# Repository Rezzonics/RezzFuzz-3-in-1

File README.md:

# RezzFuzz-3-in-1
Rezz-Fuzz 3 in 1: RAT + βr + Octaver

Eagle CAD files: 
  - Schematics 
  - BoM 
  - PCB 
  - Gerbers

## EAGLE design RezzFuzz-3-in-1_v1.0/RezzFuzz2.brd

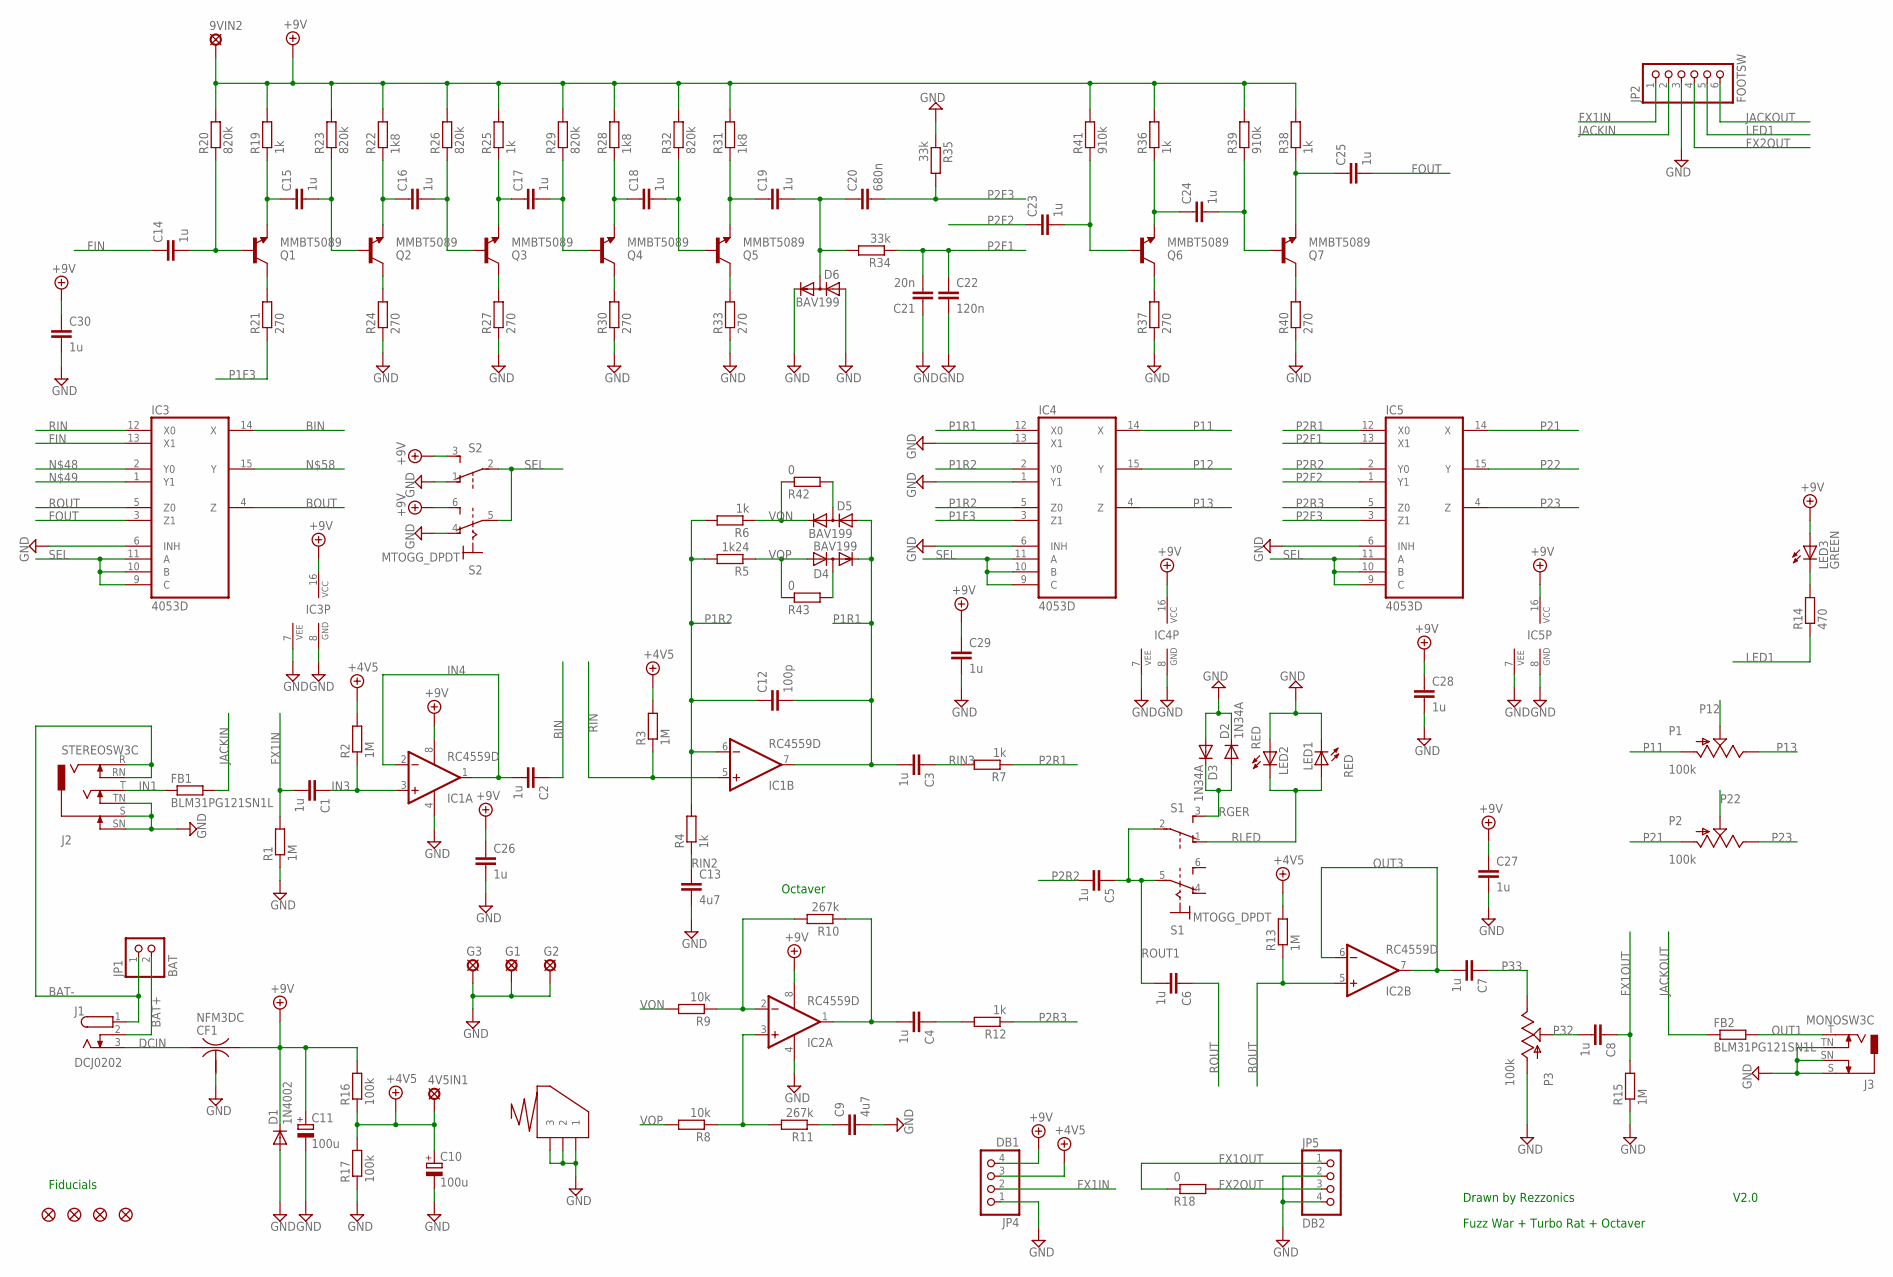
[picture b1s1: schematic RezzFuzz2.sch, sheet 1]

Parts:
4V5IN1, 9VIN2: LSP13; MPN *
BS1: CLIPAAA-; MPN *
C1, C2, C3, C4, C5, C6, C7, C8, C14, C15, C16, C17, C18, C19, C23, C24, C25, C26, C27, C28, C29, C30: 1u; C0603; MPN GRM188R61E105KA12J
C9, C13: 4u7; C0805; MPN GRM21BR61E475MA12L
C10, C11: 100u; PANASONIC_D; MPN AVE107M25X16T-F
C12: 100p; C0603; MPN VJ0603Y101MXXCW1BC
C20: 680n; C0603; MPN C0603C684K4PACTU
C21: 20n; C0603; MPN VJ0603Y223KXXCW1BC
C22: 120n; C0603; MPN GRM188R71E124KA01D
CF1: NFM3DC; MPN NFM3DPC223R1H3L
D1: 1N4002; DO41-7.6; MPN 1N4002E-E3/73
D2, D3: 1N34A; DO35-7; MPN 1n34A
D4, D5, D6: BAV199; SOT23; MPN BAV199,235
FB1, FB2: BLM31PG121SN1L; R1206; MPN BLM31PG121SN1L
G1, G2, G3: LSP13; MPN *
IC1, IC2: RC4559D; SO08; MPN RC4559DE4
IC3, IC4, IC5: 4053D; SO16; MPN CD4053BM96G3
J1: DCJ0202; MPN 163-179PH-EX
J2: STEREOSW3C; NEUTRIK-NMJ6HCD2; MPN NMJ6HCD2
J3: MONOSW3C; NEUTRIK-NMJ4HCD2; MPN NMJ4HCD2
JP1: BAT; 1X02; MPN 929834-01-02-RK
JP2: FOOTSW; 1X06; MPN 929834-01-04-RK
JP3, JP6, JP7, JP8: FIDUCIAL1X2.5; FIDUCIAL-1X2.5; MPN *
JP4: DB1; 1X04; MPN 929834-01-04-RK
JP5: DB2; 1X04; MPN 929834-01-04-RK
LED1, LED2: RED; CHIPLED_1206; MPN 598-8210-107F
LED3: GREEN; LED5MM; MPN C5SMF-GJS-CV14Q7S1
P1, P2: 100k; POT_MAMMOTH; MPN RV16AF-41-15R1-B100K
P3: 100k; POT_MAMMOTH; MPN RV16AF-41-15R1-A100K
Q1, Q2, Q3, Q4, Q5, Q6, Q7: MMBT5089; SOT23; MPN MMBT5089
R1, R2, R3, R13, R15: 1M; R0603; MPN CR0603-FX-1004ELF
R4: 1k; R0603; MPN CR0603-FX-1004ELF
R5: 1k24; R0603; MPN CR0603-FX-1241ELF
R6, R7, R12: 1k; R0603; MPN CR0603-FX-1001HLF
R8, R9: 10k; R0603; MPN CR0603-FX-1002HLF
R10, R11: 267k; R0603; MPN CR0603-FX-2673ELF
R14: 470; R0603; MPN CR0603-FX-4700ELF
R16, R17: 100k; R0603; MPN CR0603-FX-1003ELF
R18, R42, R43: 0; R0603; MPN CRCW06030000ZSTB
R19, R25: 1k; R0603; MPN CR0603-FX-1003ELF
R20, R23, R26, R29, R32: 820k; R0603; MPN CR0603-FX-4303ELF
R21, R24, R27, R30, R33, R37, R40: 270; R0603; MPN CR0603-FX-3900ELF
R22, R28, R31: 1k8; R0603; MPN CR0603-FX-1803ELF
R34, R35: 33k; R0603; MPN CR0603-FX-3302ELF
R36, R38: 1k; R0603; MPN CR0603-FX-1803ELF
R39, R41: 910k; R0603; MPN CR0603-FX-9103ELF
S1: MTOGG_DPDT; MTOGGLE_DPDT; MPN M2023SS1W03
S2: MTOGG_DPDT; MTOGGLE_DPDT; MPN M2022SS1W03

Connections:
+4.5V: 4V5IN1.MP, C10.+, JP4.3, R2.2, R3.2, R13.2, R16.1, R17.2
+9V: 9VIN2.MP, C11.+, C26.1, C27.1, C28.1, C29.1, C30.1, CF1.3, D1.C, IC1.8 (V+), IC2.8 (V+), IC3.16 (VCC), IC4.16 (VCC), IC5.16 (VCC), JP4.4, LED3.A, R16.2, R19.2, R20.2, R22.2, R23.2, R25.2, R26.2, R28.2, R29.2, R31.2, R32.2, R36.2, R38.2, R39.2, R41.2, S2.3 (S), S2.6 (S)
BAT+: J1.2, JP1.2
BAT-: J1.1, J2.R, J2.RN, JP1.1
BIN: C2.1, IC3.14 (X)
BOUT: IC2.5 (+IN), IC3.4 (Z), R13.1
DCIN: CF1.1, J1.3
FIN: C14.1, IC3.13 (X1)
FOUT: C25.2, IC3.3 (Z1)
FX1IN: C1.2, JP2.1, JP4.2, R1.2
FX1OUT: C8.1, JP5.1, R15.2, R18.1
FX2OUT: JP2.4, JP5.3, R18.2
GND: BS1.1, BS1.2, BS1.3, C9.2, C10.-, C11.-, C13.2, C21.1, C22.2, C26.2, C27.2, C28.2, C29.2, C30.2, CF1.2@1 (2), D1.A, D2.C, D3.A, D6.1 (A), D6.2 (C), G1.MP, G2.MP, G3.MP, IC1.4 (V-), IC2.4 (V-), IC3.6 (INH), IC3.7 (VEE), IC3.8 (GND), IC4.1 (Y1), IC4.6 (INH), IC4.7 (VEE), IC4.8 (GND), IC4.13 (X1), IC5.6 (INH), IC5.7 (VEE), IC5.8 (GND), J2.S, J2.SN, J2.TN, J3.S, J3.SN, J3.TN, JP2.3, JP4.1, JP5.2, JP5.4, LED1.C, LED2.A, P3.P$1 (A), R1.1, R15.1, R17.1, R24.1, R27.1, R30.1, R33.1, R35.1, R37.1, R40.1, S2.1 (O), S2.4 (O)
IN1: FB1.1, J2.T
IN3: C1.1, IC1.3 (+IN), R2.1
IN4: C2.2, IC1.1 (OUT), IC1.2 (-IN)
JACKIN: FB1.2, JP2.2
JACKOUT: FB2.1, JP2.6
LED1: JP2.5, R14.1
unnamed: C14.2, Q1.1 (B), R20.1
unnamed: Q1.3 (C), R21.2
unnamed: C16.1, Q2.2 (E), R22.1
unnamed: Q2.3 (C), R24.2
unnamed: C16.2, Q3.1 (B), R26.1
unnamed: C17.1, Q3.2 (E), R25.1
unnamed: IC2.3 (+IN), R8.1, R11.2
unnamed: IC2.2 (-IN), R9.1, R10.2
unnamed: C9.1, R11.1
unnamed: C4.2, IC2.1 (OUT), R10.1
unnamed: C4.1, R12.2
unnamed: Q3.3 (C), R27.2
unnamed: C17.2, Q4.1 (B), R29.1
unnamed: C18.1, Q4.2 (E), R28.1
unnamed: Q4.3 (C), R30.2
unnamed: C18.2, Q5.1 (B), R32.1
unnamed: C19.1, Q5.2 (E), R31.1
unnamed: D5.3 (AC), R42.2
unnamed: Q5.3 (C), R33.2
unnamed: C19.2, C20.1, D6.3 (AC), R34.2
unnamed: C24.2, Q7.1 (B), R39.1
unnamed: C23.2, Q6.1 (B), R41.1
unnamed: C24.1, Q6.2 (E), R36.1
unnamed: C25.1, Q7.2 (E), R38.1
unnamed: Q7.3 (C), R40.2
unnamed: Q6.3 (C), R37.2
unnamed: LED3.K (C), R14.2
unnamed: C15.2, Q2.1 (B), R23.1
unnamed: D4.3 (AC), R43.2
unnamed: C15.1, Q1.2 (E), R19.1
OUT1: FB2.2, J3.T
OUT3: C7.2, IC2.6 (-IN), IC2.7 (OUT)
P1F3: IC4.3 (Z1), R21.1
P1R1: C3.2, C12.2, D4.2 (C), D5.1 (A), IC1.7 (OUT), IC4.12 (X0)
P1R2: C12.1, IC1.6 (-IN), IC4.2 (Y0), IC4.5 (Z0), R4.2, R5.2, R6.2
P2F1: C21.2, C22.1, IC5.13 (X1), R34.1
P2F2: C23.1, IC5.1 (Y1)
P2F3: C20.2, IC5.3 (Z1), R35.2
P2R1: IC5.12 (X0), R7.1
P2R2: C5.2, IC5.2 (Y0)
P2R3: IC5.5 (Z0), R12.1
P11: IC4.14 (X), P1.P$1 (A)
P12: IC4.15 (Y), P1.P$2 (S)
P13: IC4.4 (Z), P1.P$3 (E)
P21: IC5.14 (X), P2.P$1 (A)
P22: IC5.15 (Y), P2.P$2 (S)
P23: IC5.4 (Z), P2.P$3 (E)
P32: C8.2, P3.P$2 (S)
P33: C7.1, P3.P$3 (E)
RGER: D2.A, D3.C, S1.3 (S)
RIN: IC1.5 (+IN), IC3.12 (X0), R3.1
RIN2: C13.1, R4.1
RIN3: C3.1, R7.2
RLED: LED1.A, LED2.C, S1.1 (O)
ROUT: C6.1, IC3.5 (Z0)
ROUT1: C5.1, C6.2, S1.2, S1.5
SEL: IC3.9 (C), IC3.10 (B), IC3.11 (A), IC4.9 (C), IC4.10 (B), IC4.11 (A), IC5.9 (C), IC5.10 (B), IC5.11 (A), S2.2, S2.5
VON: D5.2 (C), R6.1, R9.2, R42.1
VOP: D4.1 (A), R5.1, R8.2, R43.1

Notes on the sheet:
Drawn by Rezzonics
Octaver
Fiducials
V2.0
Fuzz War + Turbo Rat + Octaver

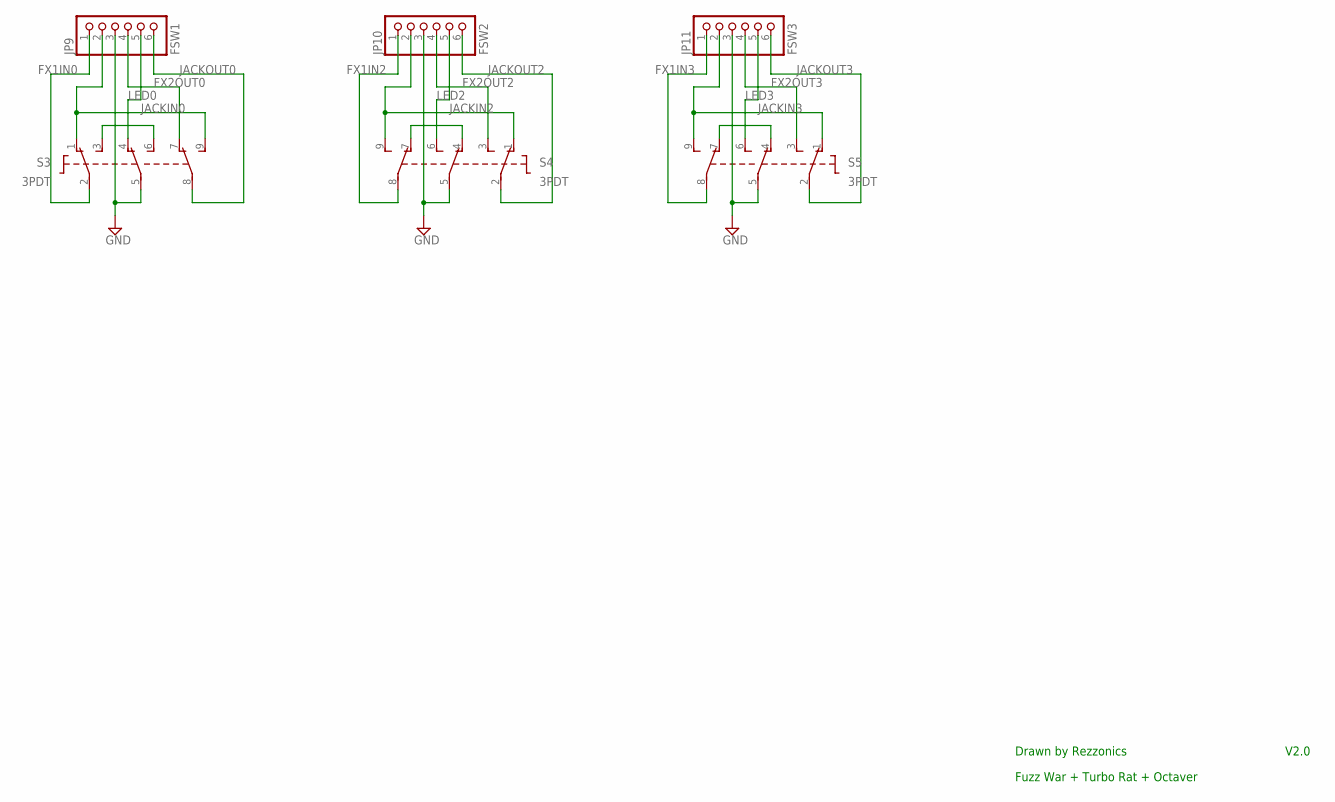
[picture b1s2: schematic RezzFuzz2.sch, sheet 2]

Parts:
JP9: FSW1; 1X06; MPN *
JP10: FSW2; 1X06; MPN *
JP11: FSW3; 1X06; MPN *
S3, S4, S5: 3PDT; MPN *

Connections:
FX1IN0: JP9.1, S3.2 (P1)
FX1IN2: JP10.1, S4.8 (P3)
FX1IN3: JP11.1, S5.8 (P3)
FX2OUT0: JP9.4, S3.7 (O3)
FX2OUT2: JP10.4, S4.3 (S1)
FX2OUT3: JP11.4, S5.3 (S1)
GND1: JP9.3, S3.5 (P2)
GND2: JP10.3, S4.5 (P2)
GND3: JP11.3, S5.5 (P2)
JACKIN0: JP9.2, S3.1 (O1), S3.9 (S3)
JACKIN2: JP10.2, S4.1 (O1), S4.9 (S3)
JACKIN3: JP11.2, S5.1 (O1), S5.9 (S3)
JACKOUT0: JP9.6, S3.8 (P3)
JACKOUT2: JP10.6, S4.2 (P1)
JACKOUT3: JP11.6, S5.2 (P1)
LED0: JP9.5, S3.4 (O2)
LED2: JP10.5, S4.6 (S2)
LED3: JP11.5, S5.6 (S2)
unnamed: S3.3 (S1), S3.6 (S2)
unnamed: S4.4 (O2), S4.7 (O3)
unnamed: S5.4 (O2), S5.7 (O3)

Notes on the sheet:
Drawn by Rezzonics
V2.0
Fuzz War + Turbo Rat + Octaver

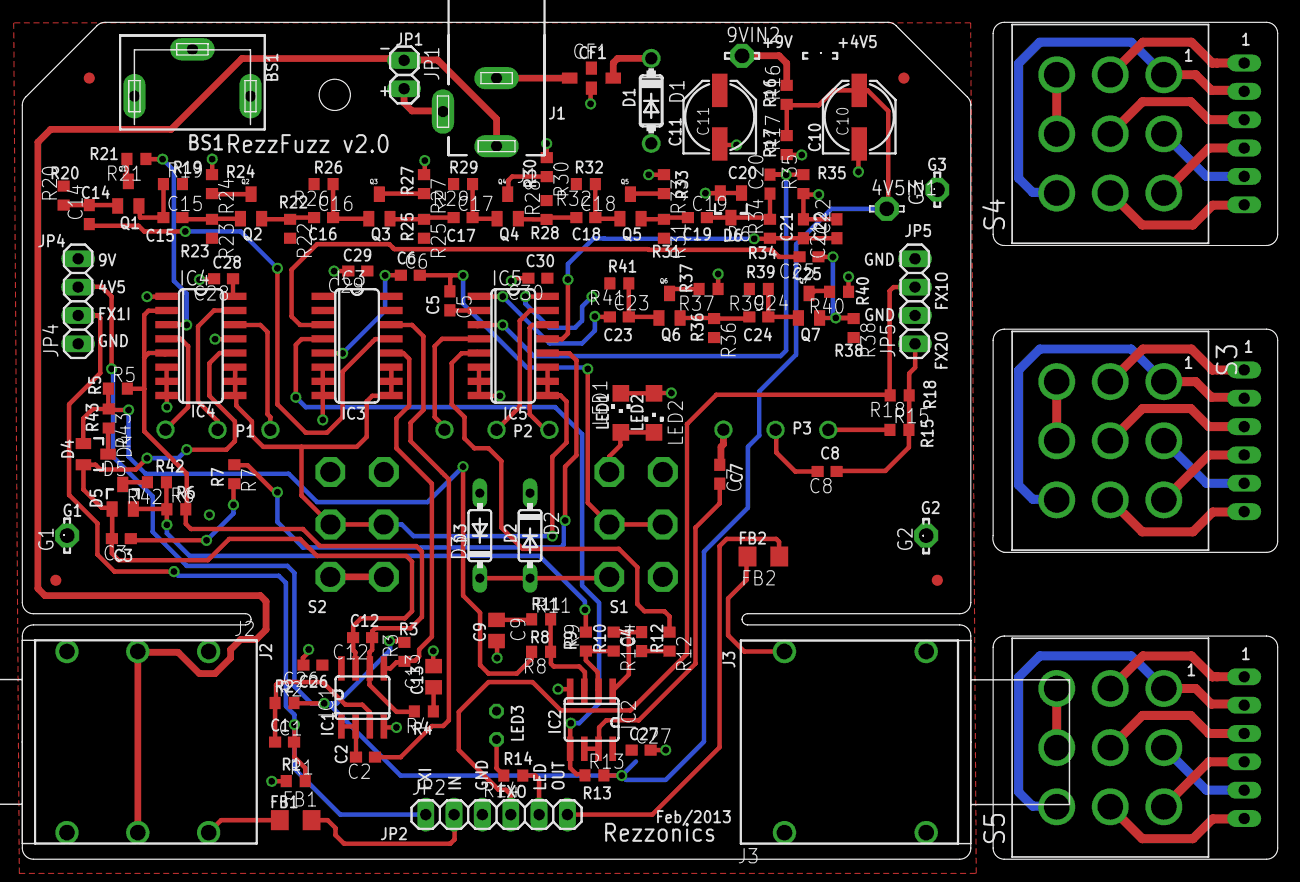
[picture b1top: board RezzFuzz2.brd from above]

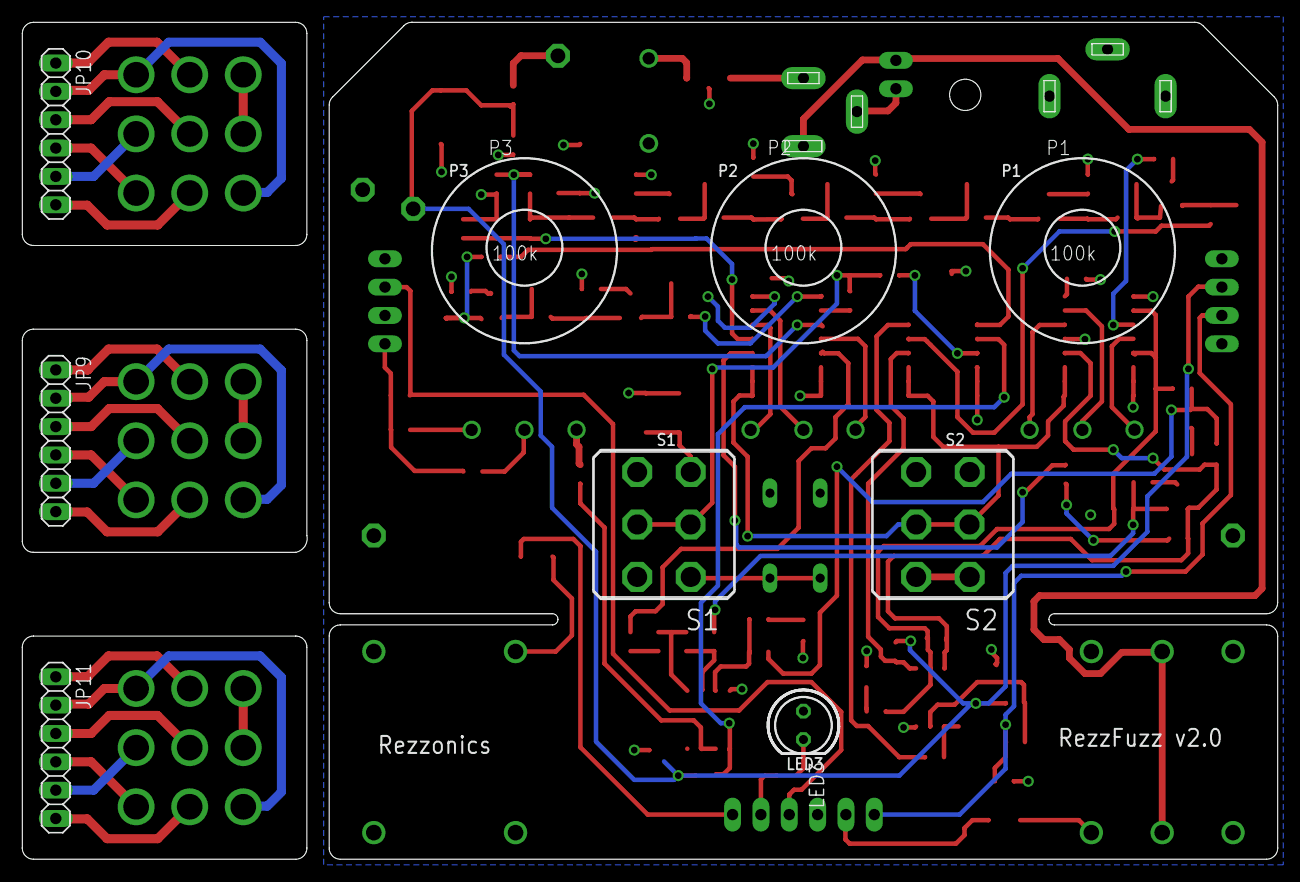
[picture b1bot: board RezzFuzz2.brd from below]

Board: 2 copper layers, 85.0 x 75.0 mm, 125 parts (9 on the bottom side), 99 nets.

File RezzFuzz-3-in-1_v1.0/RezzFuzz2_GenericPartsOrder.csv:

Part Number,Mfg Name,VID,Vendor Part Num,Description,Customer Ref,Part Value,Tol,Qty-1,Qty-5,Qty-25,Part References,Value
CRCW06030000ZSTB,Vishay,ME,71-CRCW0603000ZT-RT5,Thick Film Resistors - SMD 1/10watt ZEROohm Jumper,res013,0,*,3,15,75,"R18, R42, R43",0
CR0603-FX-1003ELF,Bourns,ME,652-CR0603-FX-103ELF,Thick Film Resistors - SMD 100K 1% 1/10 WATT,res004,100k,*,1,5,25,"R25",1.2k
CR0603-FX-1803ELF,Bourns,ME,652-CR0603FX-1803ELF,Thick Film Resistors - SMD 180K 1% 1/10W,res006,180k,*,5,25,125,"R22, R28, R31, R36, R38",1.2k
CR0603-FX-1004ELF,Bourns,ME,652-CR0603FX-1004ELF,Thick Film Resistors - SMD 1M 1% 1/10W,res003,1M,*,5,25,125,"R1, R2, R3, R13, R15",1M
*** ERROR - PART '1n34A' NOT FOUND FOR: "D2, D3"
1N4002E-E3/73,Vishay,ME,625-1N4002E-E3/73,Rectifiers Vr/100V Io/1A,diode001,*,*,1,5,25,"D1",1N4002
CR0603-FX-1001HLF,Bourns,ME,652-CR0603-FX1001HLF,Thick Film Resistors - SMD 1KOHM 1/10WATT 1%,res001,1k,*,3,15,75,"R6, R7, R12",1k
CR0603-FX-1004ELF,Bourns,ME,652-CR0603FX-1004ELF,Thick Film Resistors - SMD 1M 1% 1/10W,res003,1M,*,1,5,25,"R4",1k
CR0603-FX-1241ELF,Bourns,ME,652-CR0603FX-1241ELF,Thick Film Resistors - SMD 1.24K 1% 1/10W,res005,1.24k,*,1,5,25,"R5",1k24
GRM188R61E105KA12J,Murata,ME,81-GRM188R61E105KA2J,Multilayer Ceramic Capacitors MLCC - SMD/SMT 1.0uF 25Volts 10%,capcer004,1u,10%,17,85,425,"C1, C2, C3, C4, C5, C6, C7, C8, C14, C15, C16, C17, C18, C19, C23, C24, C25",1u
CR0603-FX-1003ELF,Bourns,ME,652-CR0603-FX-103ELF,Thick Film Resistors - SMD 100K 1% 1/10 WATT,res004,100k,*,1,5,25,"R19",3.3k
*** ERROR - PART '*' NOT FOUND FOR: "S3, S4, S5"
GRM21BR61E475MA12L,Murata,ME,81-GRM21BR61E475MA2L,Multilayer Ceramic Capacitors MLCC - SMD/SMT 4.7uF 25Volts 20%,capcer006,4.7u,20%,2,10,50,"C9, C13",4u7
CR0603-FX-1002HLF,Bourns,ME,652-CR0603-FX1002HLF,Thick Film Resistors - SMD 10KOHM 1/10WATT 1%,res002,10k,*,2,10,50,"R8, R9",10k
VJ0603Y223KXXCW1BC,Vishay,ME,77-VJ0603Y223KXXCBC,Multilayer Ceramic Capacitors MLCC - SMD/SMT 0603 0.022uF 25volts X7R 10%,capcer002,22n,10%,1,5,25,"C21",20n
CR0603-FX-3302ELF,Bourns,ME,652-CR0603FX-3302ELF,Thick Film Resistors - SMD 33K ohm 1%,res008,33k,*,2,10,50,"R34, R35",33k
CR0603-FX-1003ELF,Bourns,ME,652-CR0603-FX-103ELF,Thick Film Resistors - SMD 100K 1% 1/10 WATT,res004,100k,*,2,10,50,"R16, R17",100k
*** ERROR - PART 'RV16AF-41-15R1-A100K' NOT FOUND FOR: "P3"
*** ERROR - PART 'RV16AF-41-15R1-B100K' NOT FOUND FOR: "P1, P2"
VJ0603Y101MXXCW1BC,Vishay,ME,77-VJ0603Y101MXXCBC,Multilayer Ceramic Capacitors MLCC - SMD/SMT 0603 100pF 25volts X7R 20%,capcer001,100p,20%,1,5,25,"C12",100p
AVE107M25X16T-F,CornellDubilier,ME,598-AVE107M25X16T-F,Aluminium Electrolytic Capacitors - SMD 100uF 25V 85C,capelec001,100u,*,2,10,50,"C10, C11",100u
GRM188R71E124KA01D,Murata,ME,81-GRM188R71E124KA1D,Multilayer Ceramic Capacitors MLCC - SMD/SMT 0.12uF 25Volts X7R 10%,capcer005,120n,10%,1,5,25,"C22",120n
CR0603-FX-2673ELF,Bourns,ME,652-CR0603FX-2673ELF,Thick Film Resistors - SMD 267K ohm 1%,res007,267k,*,2,10,50,"R10, R11",267k
CR0603-FX-3900ELF,Bourns,ME,652-CR0603FX-3900ELF,Thick Film Resistors - SMD 390 ohm 1%,res009,390,*,7,35,175,"R21, R24, R27, R30, R33, R37, R40",270
CR0603-FX-4700ELF,Bourns,ME,652-CR0603FX-4700ELF,Thick Film Resistors - SMD 470 ohm 1%,res011,470,*,1,5,25,"R14",470
C0603C684K4PACTU,Kemet,ME,80-C0603C684K4P,Multilayer Ceramic Capacitors MLCC - SMD/SMT 16volts 0.68uF X5R 10%,capcer003,680n,10%,1,5,25,"C20",680n
CR0603-FX-4303ELF,Bourns,ME,652-CR0603FX-4303ELF,Thick Film Resistors - SMD 430K ohm 1%,res010,430k,*,5,25,125,"R20, R23, R26, R29, R32",820k
CR0603-FX-9103ELF,Bourns,ME,652-CR0603FX-9103ELF,Thick Film Resistors - SMD 910K ohm 1%,res012,910k,*,2,10,50,"R39, R41",910k
1267,Keystone electronics,ME,534-1267,Terminals TERMINAL .110X.020,con013,1267,*,1,5,25,"9VIN2",1267
CD4053BM96G3,TexasInstruments,ME,595-CD4053BM96G3,Multiplexer E19Switch ICs CMOS Triple 2Ch Ana Mux/Demux,iclog001,4053,*,3,15,75,"IC3, IC4, IC5",4053D
*** ERROR - PART '929834-01-02-RK' NOT FOUND FOR: "JP1"
BAV199,235,NXP,ME,771-BAV199235,Rectifiers DIODE LOW LEAKAGE,diode002,BAV199,*,3,15,75,"D4, D5, D6",BAV199
BLM31PG121SN1L,Murata,ME,81-BLM31PG121SN1L,EMI Filter Beads, Chips & Arrays 1206 120 OHM,fer002,120,*,2,10,50,"FB1, FB2",BLM31PG121SN1L
12BH629-GR,Eagle Plastic Devices,ME,12BH629-GR,Cylindrical Battery Contacts, Clips, Holders & Springs AA/AAA SPRING CONT,con014,*,*,1,5,25,"BS1",CLIPAAA-
*** ERROR - PART '929834-01-04-RK' NOT FOUND FOR: "JP4"
*** ERROR - PART '929834-01-04-RK' NOT FOUND FOR: "JP5"
163-179PH-EX,Kobiconn,ME,163-179PH-EX,DC Power Connectors PCB 2.1MM,con001,*,*,1,5,25,"J1",DCJ0202
*** ERROR - PART '*' NOT FOUND FOR: "JP3, JP6, JP7, JP8"
*** ERROR - PART '929834-01-04-RK' NOT FOUND FOR: "JP2"
*** ERROR - PART '*' NOT FOUND FOR: "JP9"
*** ERROR - PART '*' NOT FOUND FOR: "JP10"
*** ERROR - PART '*' NOT FOUND FOR: "JP11"
C5SMF-GJS-CV14Q7S1,Cree,Inc.,ME,941-C5SMFGJSCV14Q7S1,Standard LED - Through Hole Green Oval LED ,led002,GREEN,*,1,5,25,"LED3",GREEN
1267,Keystone electronics,ME,534-1267,Terminals TERMINAL .110X.020,con013,1267,*,6,30,150,"4V5IN1, G1, G2, G3, IN1, OUT1",LSP13
MMBT5089,Fairchild Semiconductor,ME,512-MMBT5089,Transistors Bipolar - BJT NPN Transistor General Purpose ,bjt001,MMBT5089,*,7,35,175,"Q1, Q2, Q3, Q4, Q5, Q6, Q7",MMBT5089
NMJ4HCD2,REAN,ME,550-12202,Phone Connectors 2C MONO 2-SPST NC,con005,*,*,1,5,25,"J3",MONOSW3C
M2022SS1W03,NKKSwitches,ME,633-M202203,Toggle Switches ON-NONE-ON PC DPDT,sw0001,M2022SS1W03,*,1,5,25,"S2",MTOGG_DPDT
*** ERROR - PART 'M2023SS1W03' NOT FOUND FOR: "S1"
NFM3DPC223R1H3L,Murata,ME,81-NFM3DPC223R1H3L,EMI/RFI Suppressors & Ferrites 0.022uF 50V 2A',fer001,22n,*,1,5,25,"CF1",NFM3DC
RC4580IDR,TexasInstruments,ME,595-RC4580IDR,Operational Amplifiers - Op Amps Dual Hi-Performance Op Amp,icopamp004,RC4580ID,*,2,10,50,"IC1, IC2",RC4580ID
598-8210-107F,Dialight,ME,645-598-8210-107F,Standard LED - SMD Red Water Clr 80mcd 640nm,led001,RED,*,2,10,50,"LED1, LED2",RED
NMJ6HCD2,REAN,ME,550-22302,Phone Connectors STEREO CHROME NOSE,con006,*,*,1,5,25,"J2",STEREOSW3C

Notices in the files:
parts and their libraries:
SparkFun: Licensing: CC v3.0 Share-Alike You are welcome to use this library for commercial purposes.
